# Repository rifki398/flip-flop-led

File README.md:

# Flip Flop LED
This project provides schematic and PCB layout of a simple **Flip Flop LED circuit** using basic electronic components. The circuit alternately turns LEDs on and off (blinking pattern), often used for learning the basics of electronics, digital logic, and timing circuits.
<table>
  <tr>
    <td align="center">
      
      <br/>Front View of The Board
    </td>
    <td align="center">
      
      <br/>Back View of The Board
    </td>
  </tr>
</table>

---

## Features
- Alternating LED blinking (Flip Flop behavior)  
- Easy to change time constant based on resistance and capacitance values  
- Educational project for beginners in electronics  

---

## Components Used
- 2 × LEDs (any color)  
- 2 × Resistors 100-330Ω
- 2 x Resistors 1k-5kΩ
- 1 × NPN Transistor (e.g., 2N2222 or BC547)  
- 1 × Capacitor 100uF
- 1 × Battery Coin 3V (CR2032)
- 1 x Slide switch SS12D10

---

## Circuit Diagram
The flip flop effect can be achieved using a pair of transistors with cross-coupled capacitors.

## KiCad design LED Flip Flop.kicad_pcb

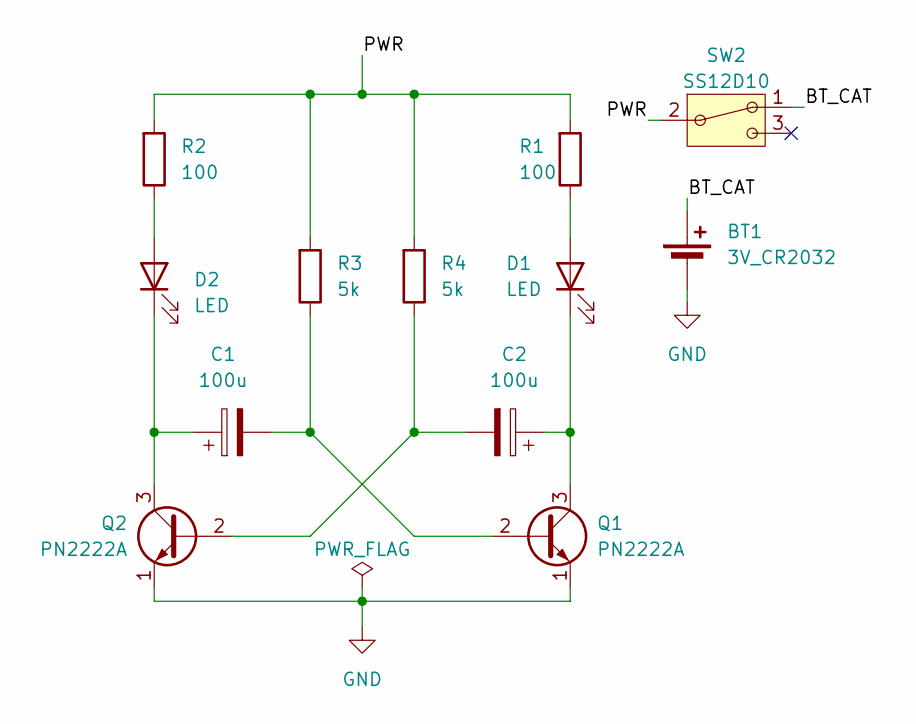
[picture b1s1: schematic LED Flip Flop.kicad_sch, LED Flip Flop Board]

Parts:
BT1: 3V_CR2032; BatteryHolder_MYOUNG_BS-07-A1BJ001_CR2032
C1, C2: 100u; C_Radial_D6.3mm_H11.0mm_P2.50mm
D1, D2: LED; LED_D5.0mm
Q1, Q2: PN2222A; TO-92_Inline
R1, R2: 100; R_Axial_DIN0207_L6.3mm_D2.5mm_P10.16mm_Horizontal
R3, R4: 5k; R_Axial_DIN0207_L6.3mm_D2.5mm_P10.16mm_Horizontal
SW2: SS12D10; SS12D10_THT_12.7x6.7mm_P4.7mm

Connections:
/BT_CAT: BT1.1 (+), SW2.1
/PWR: R1.1, R2.1, R3.1, R4.1, SW2.2
GND: BT1.2 (-), Q1.1 (E), Q2.1 (E)
unnamed: D1.2 (A), R1.2
unnamed: C2.1, D1.1 (K), Q1.3 (C)
unnamed: D2.2 (A), R2.2
unnamed: C1.1, D2.1 (K), Q2.3 (C)
unnamed: C1.2, Q1.2 (B), R3.2
unnamed: C2.2, Q2.2 (B), R4.2

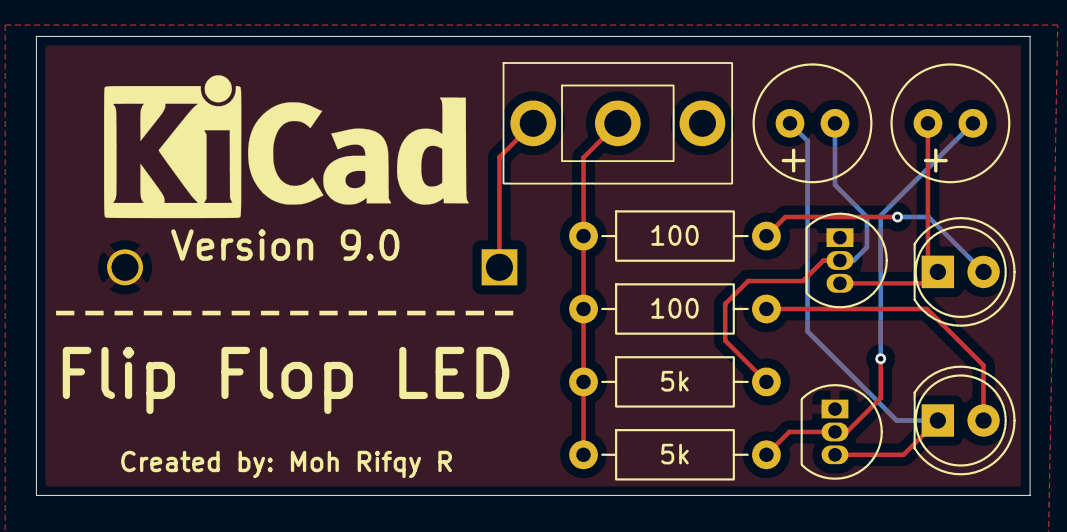
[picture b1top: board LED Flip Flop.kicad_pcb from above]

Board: 2 copper layers, 55.2 x 25.5 mm, 12 parts (1 on the bottom side), 9 nets.
